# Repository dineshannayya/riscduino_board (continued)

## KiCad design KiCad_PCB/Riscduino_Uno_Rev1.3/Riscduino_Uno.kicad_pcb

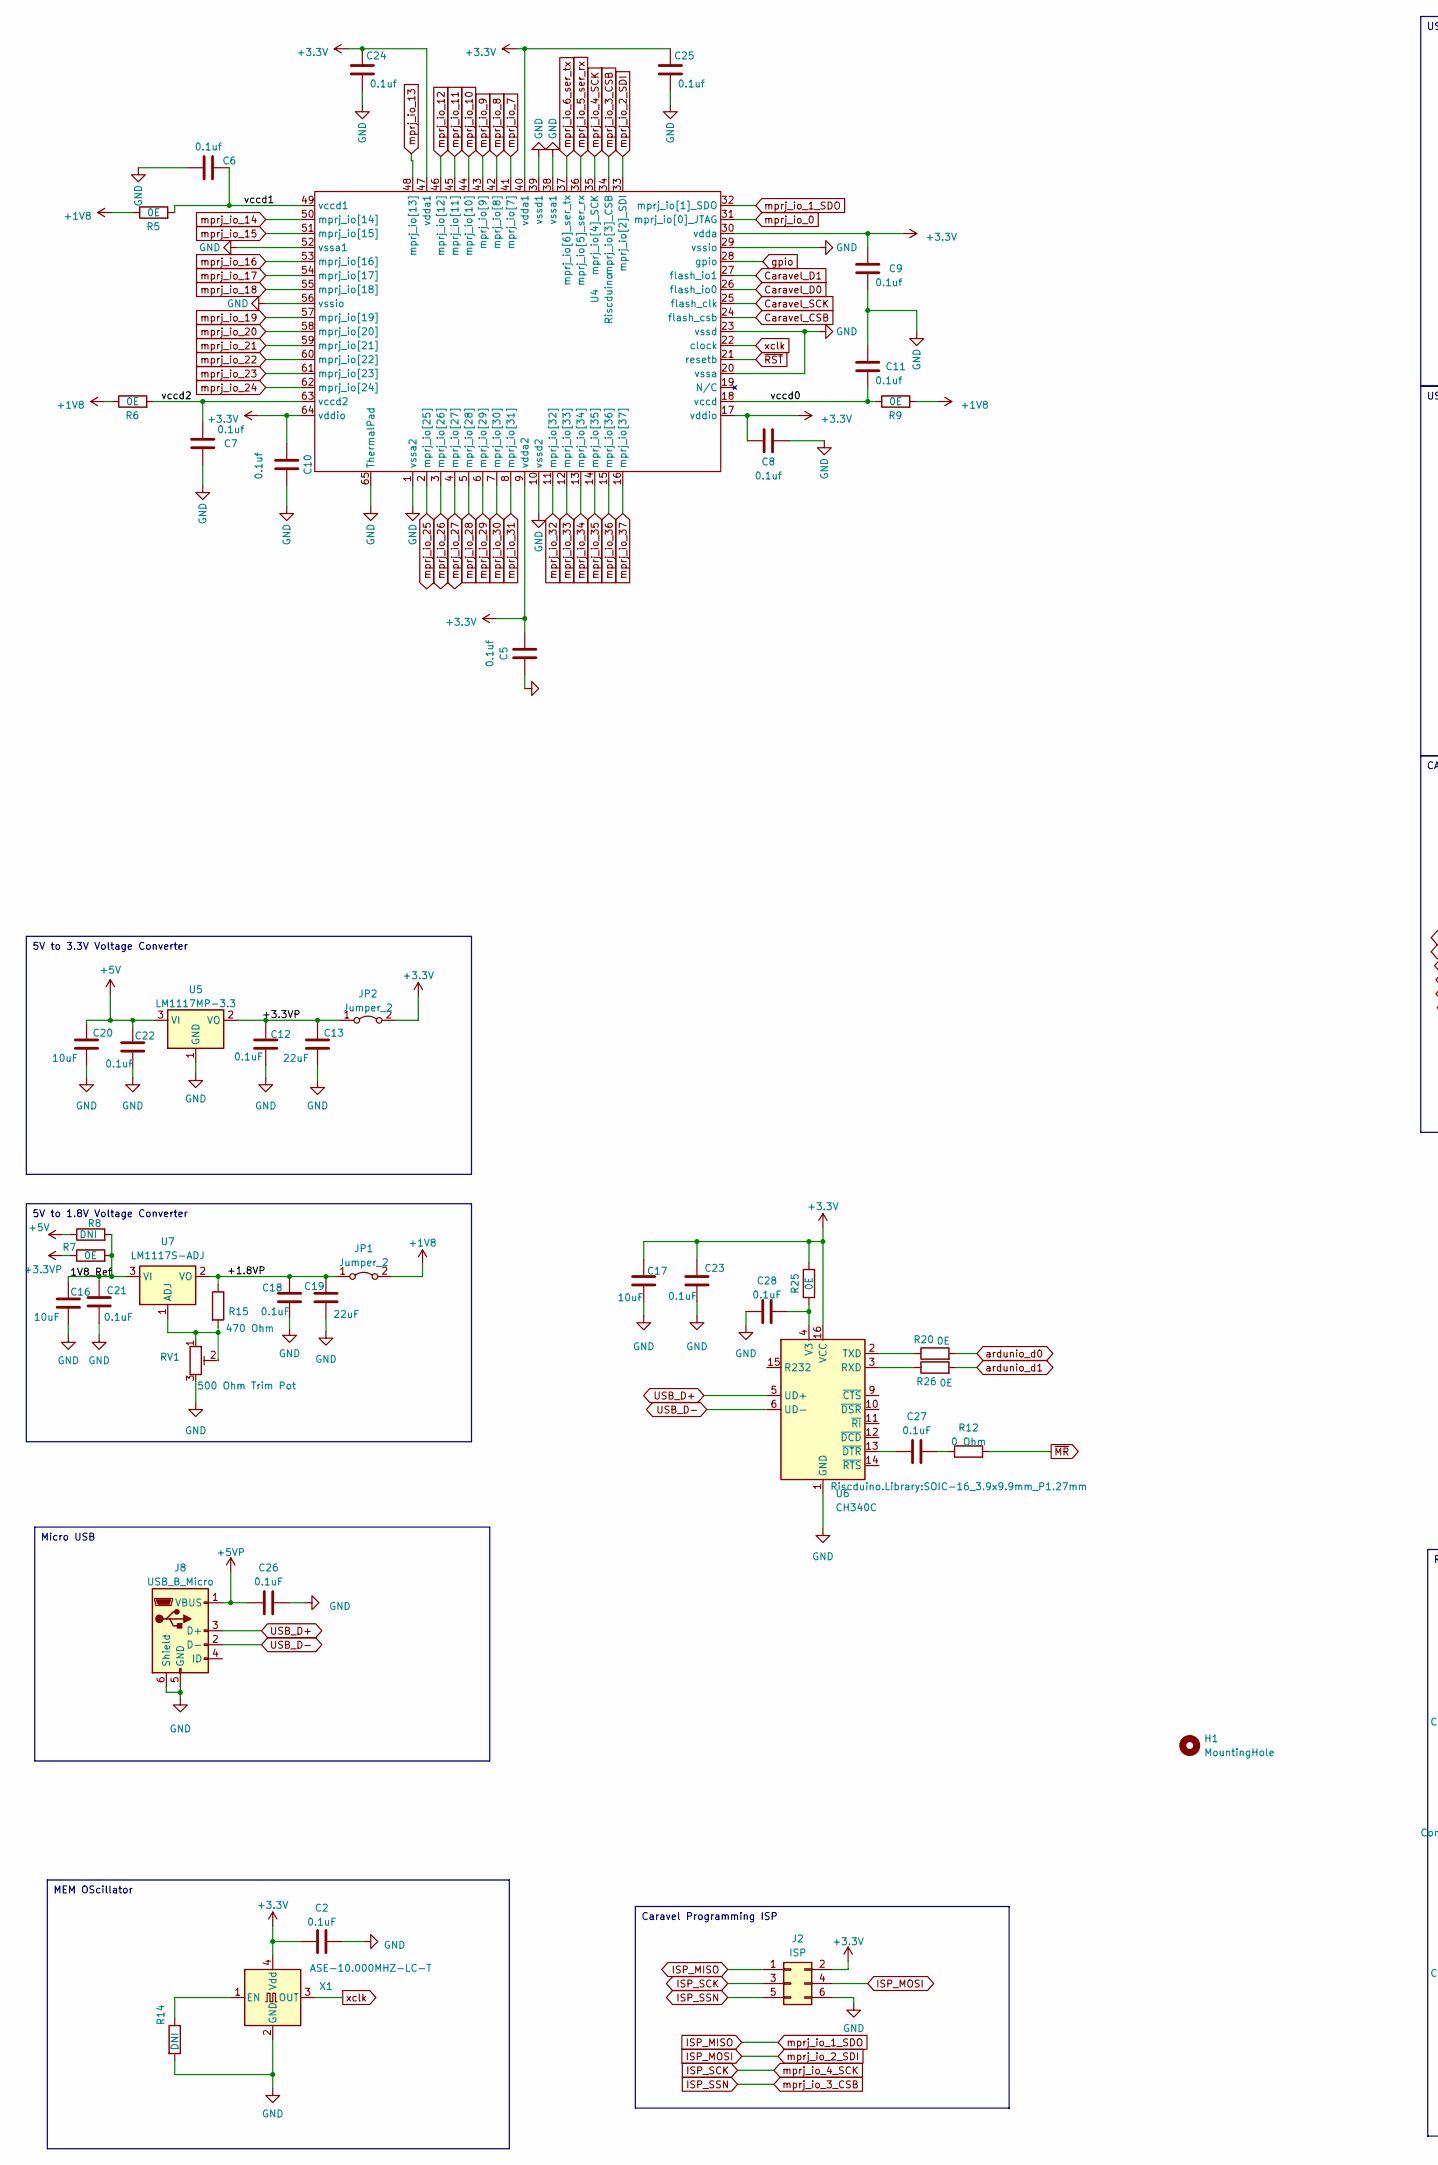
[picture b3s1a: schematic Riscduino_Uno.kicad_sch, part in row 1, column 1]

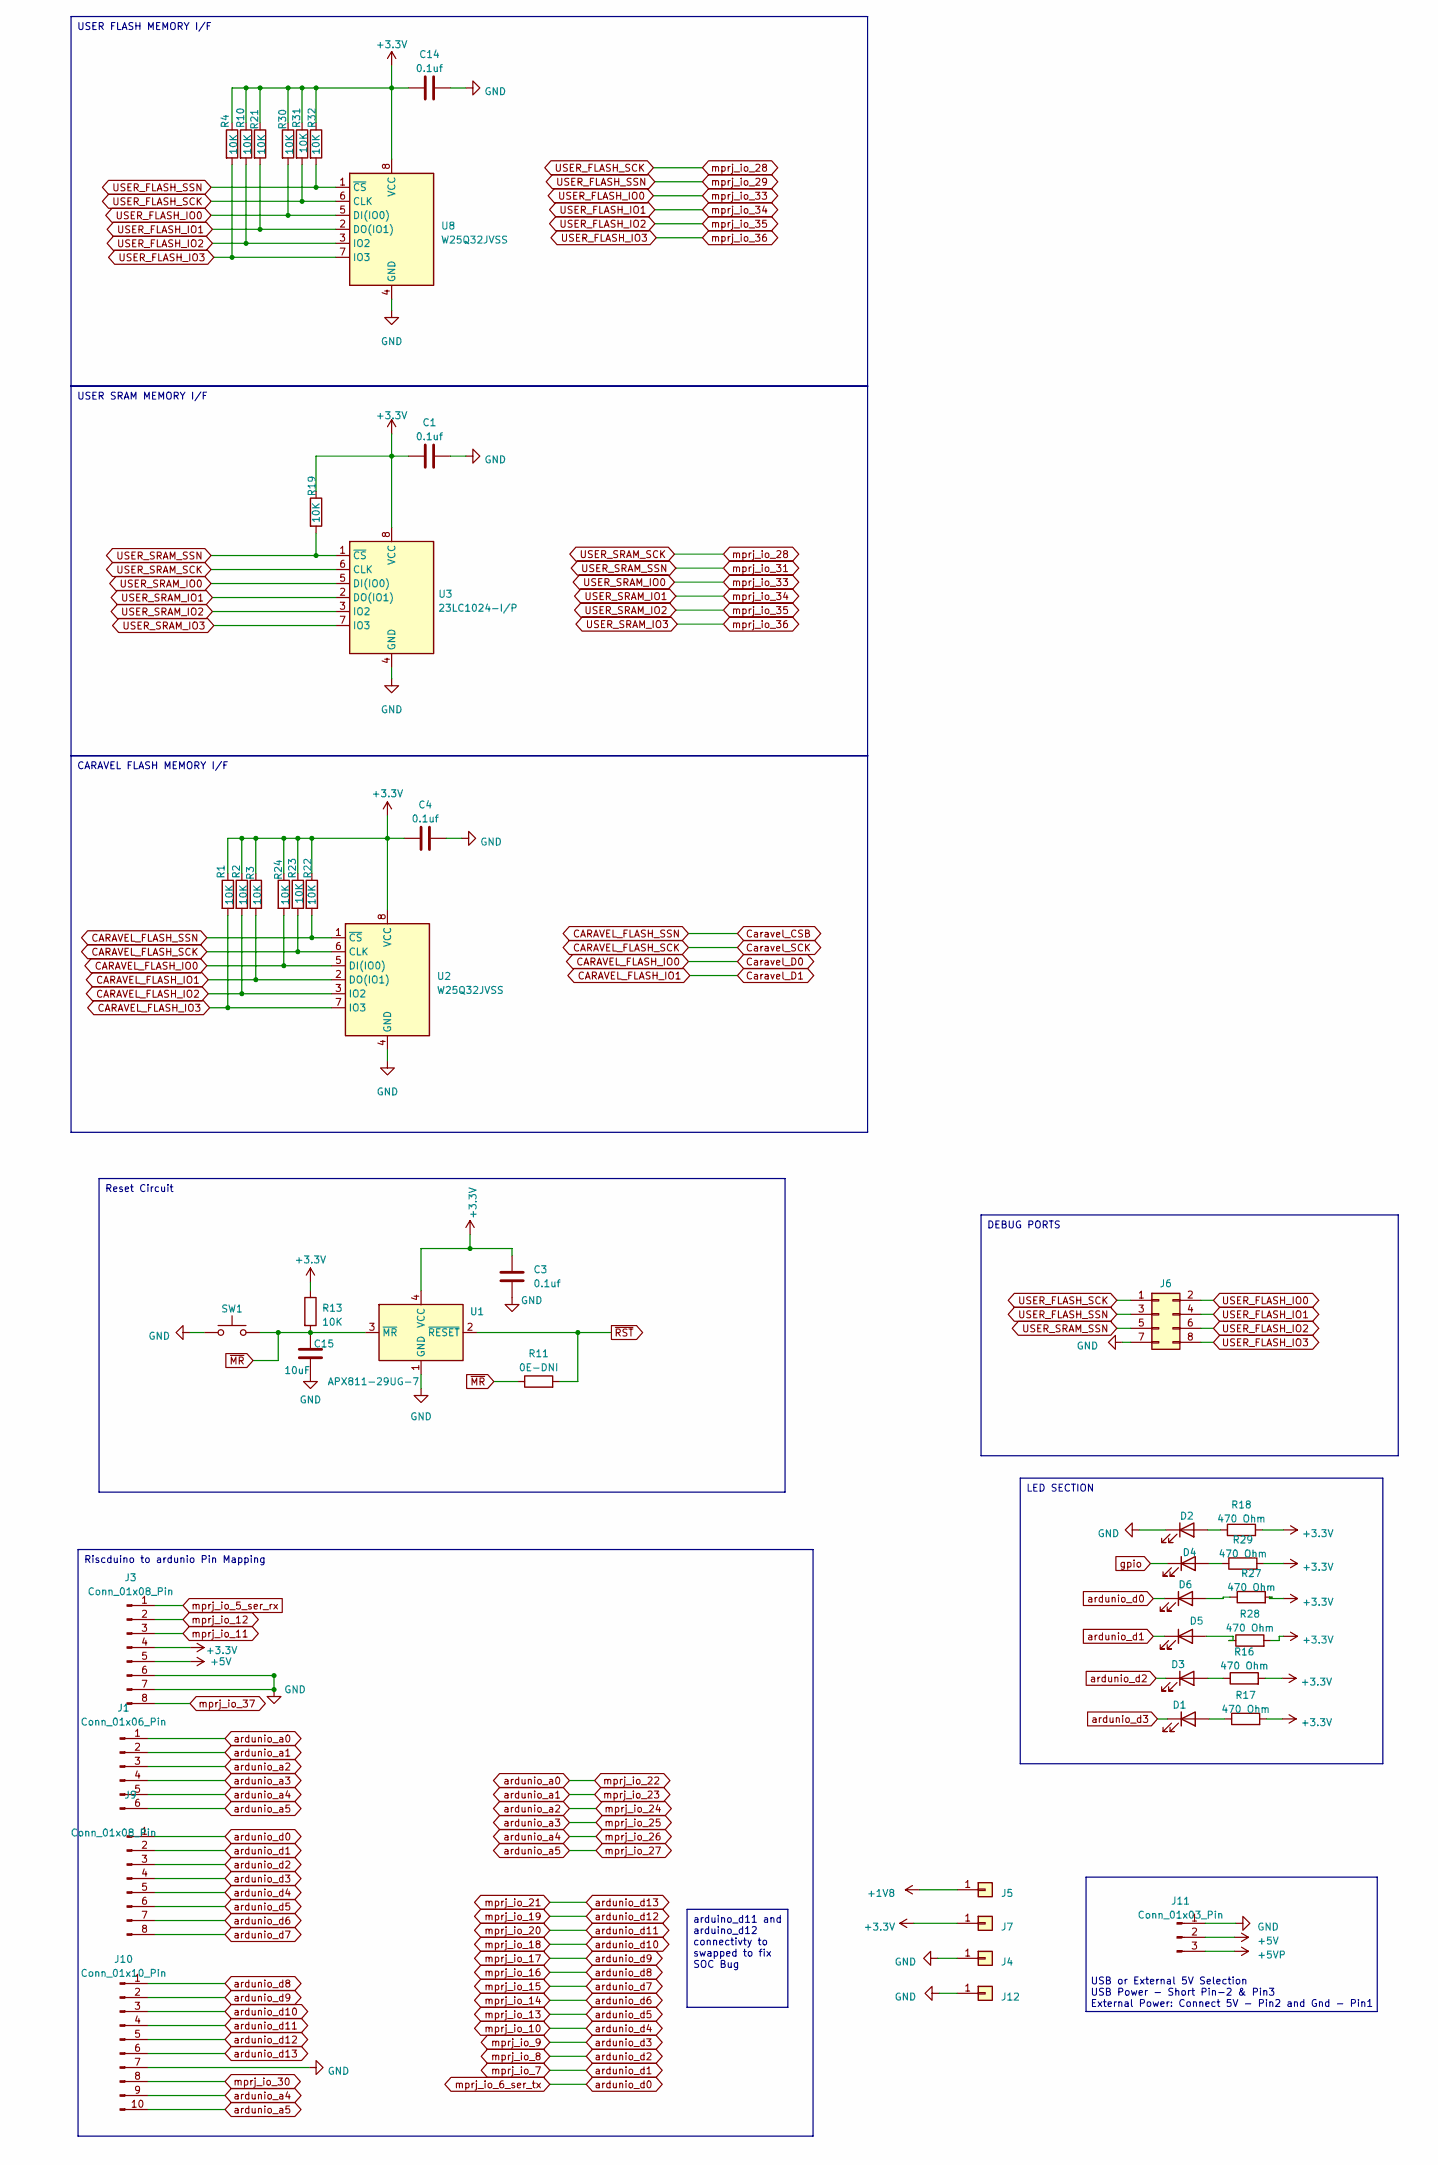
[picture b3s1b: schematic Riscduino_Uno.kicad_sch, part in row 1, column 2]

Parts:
C1, C3, C4, C5, C6, C7, C8, C9, C10, C11, C14, C24, C25: 0.1uf; C_0603_1608Metric_Pad1.08x0.95mm_HandSolder
C2, C12, C18, C21, C22, C23, C26, C27, C28: 0.1uF; C_0603_1608Metric_Pad1.08x0.95mm_HandSolder
C13, C19: 22uF; C_0805_2012Metric_Pad1.18x1.45mm_HandSolder
C15, C16, C17, C20: 10uF; C_0805_2012Metric_Pad1.18x1.45mm_HandSolder
D1, D2, D3, D4, D5: GREEN LED; LED_0805_2012Metric_Pad1.15x1.40mm_HandSolder
D6: BLUE LED; LED_0805_2012Metric_Pad1.15x1.40mm_HandSolder
H1: MountingHole; Arduino_UNO_R3_WithMountingHoles
J1: Conn_01x06_Pin; PinHeader_1x06_P2.54mm_Vertical
J2: ISP; PinHeader_2x03_P2.54mm_Vertical
J3, J9: Conn_01x08_Pin; PinHeader_1x08_P2.54mm_Vertical
J4, J5, J7, J12: Conn_01x01; PinHeader_1x01_P2.54mm_Vertical
J6: Conn_02x04_Odd_Even; PinHeader_2x04_P2.54mm_Vertical
J8: USB_B_Micro; USB_Micro-B_Molex-105017-0001
J10: Conn_01x10_Pin; PinHeader_1x10_P2.54mm_Vertical
J11: Conn_01x03_Pin; PinHeader_1x03_P2.54mm_Vertical
JP1, JP2: Jumper_2; PinHeader_1x02_P2.54mm_Vertical
R1, R2, R3, R4, R10, R13, R19, R21, R22, R23, R24, R30, R31, R32: 10K; R_0603_1608Metric_Pad0.98x0.95mm_HandSolder
R5, R6, R7, R9, R20, R25, R26: 0E; R_0603_1608Metric_Pad0.98x0.95mm_HandSolder
R8, R14: DNI; R_0603_1608Metric_Pad0.98x0.95mm_HandSolder
R11: 0E-DNI; C_0603_1608Metric_Pad1.08x0.95mm_HandSolder
R12: 0 Ohm; R_0603_1608Metric_Pad0.98x0.95mm_HandSolder
R15, R16, R17, R18, R27, R28, R29: 470 Ohm; R_0603_1608Metric_Pad0.98x0.95mm_HandSolder
RV1: 500 Ohm Trim Pot; Potentiometer_Bourns_3296W_Vertical
SW1: 4Pin Round Button SPST Straight Tactile Switch SM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; SW_SPST_EVPBF_TS4550TP
U1: APX811-29UG-7; SOT-143_Handsoldering
U2, U8: W25Q32JVSS; SOIC-8_5.23x5.23mm_P1.27mm
U3: 23LC1024-I/P; DIP-8_W7.62mm_LongPads
U4: Riscduino; RISCDUINO_QFN-64-1EP_9x9mm_P0.5mm_EP7.65x7.65mm_Ver1.1
U5: LM1117MP-3.3; SOT-223-3_TabPin2
U6: CH340C; SOIC-16_3.9x9.9mm_P1.27mm
U7: LM1117S-ADJ; SOT-223-3_TabPin2
X1: ASE-10.000MHZ-LC-T; Crystal_SMD_Abracon_ABM8G-4Pin_3.2x2.5mm

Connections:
+1V8: J5.1, JP1.2 (B), R5.1, R6.1, R9.2
+3.3V: C1.1, C2.1, C3.1, C4.1, C5.2, C8.2, C9.1, C10.2, C14.1, C17.1, C23.1, C24.1, C25.1, J2.2, J3.4, J7.1, JP2.2 (B), R1.1, R2.1, R3.1, R4.1, R10.1, R13.1, R16.2, R17.2, R18.2, R19.1, R21.1, R22.1, R23.1, R24.1, R25.2, R27.2, R28.2, R29.2, R30.1, R31.1, R32.1, U1.4 (VCC), U2.8 (VCC), U3.8 (VCC), U4.9 (vdda2), U4.17 (vddio), U4.30 (vdda), U4.40 (vdda1), U4.47 (vdda1), U4.64 (vddio), U6.16 (VCC), U8.8 (VCC), X1.4 (Vdd)
+3.3VP: C12.1, C13.1, JP2.1 (A), R7.1, U5.2 (VO)
+5V: C20.1, C22.1, J3.5, J11.2, R8.1, U5.3 (VI)
+5VP: C26.1, J8.1 (VBUS), J11.3
/+1.8VP: C18.1, C19.1, JP1.1 (A), R15.1, U7.2 (VO)
/vccd0: C11.2, R9.1, U4.18 (vccd)
/vccd1: C6.2, R5.2, U4.49 (vccd1)
/vccd2: C7.1, R6.2, U4.63 (vccd2)
CARAVEL_FLASH_IO0: R24.2, U2.5 (DI(IO0)), U4.26 (flash_io0)
CARAVEL_FLASH_IO1: R3.2, U2.2 (DO(IO1)), U4.27 (flash_io1)
CARAVEL_FLASH_IO2: R2.2, U2.3 (IO2)
CARAVEL_FLASH_IO3: R1.2, U2.7 (IO3)
CARAVEL_FLASH_SCK: R23.2, U2.6 (CLK), U4.25 (flash_clk)
CARAVEL_FLASH_SSN: R22.2, U2.1 (~CS), U4.24 (flash_csb)
GND: C1.2, C2.2, C3.2, C4.2, C5.1, C6.1, C7.2, C8.1, C9.2, C10.1, C11.1, C12.2, C13.2, C14.2, C15.2, C16.2, C17.2, C18.2, C19.2, C20.2, C21.2, C22.2, C23.2, C24.2, C25.2, C26.2, C28.1, D2.1 (K), J2.6, J3.6, J3.7, J4.1, J6.7, J8.5 (GND), J8.6 (Shield), J10.7, J11.1, J12.1, R14.2, RV1.3, SW1.1, U1.1 (GND), U2.4 (GND), U3.4 (GND), U4.1 (vssa2), U4.10 (vssd2), U4.20 (vssa), U4.23 (vssd), U4.29 (vssio), U4.38 (vssa1), U4.39 (vssd1), U4.52 (vssa1), U4.56 (vssio), U4.65 (ThermalPad), U5.1 (GND), U6.1 (GND), U8.4 (GND), X1.2 (GND)
ISP_MISO: J2.1, U4.32 (mprj_io[1]_SDO)
ISP_MOSI: J2.4, U4.33 (mprj_io[2]_SDI)
ISP_SCK: J2.3, U4.35 (mprj_io[4]_SCK)
ISP_SSN: J2.5, U4.34 (mprj_io[3]_CSB)
unnamed: C27.2, R12.1
unnamed 21: D1.2 (A), R17.1; also elsewhere on the board
unnamed: D2.2 (A), R18.1
unnamed: D3.2 (A), R16.1
unnamed: D4.2 (A), R29.1
unnamed: D5.2 (A), R28.1
unnamed: D6.2 (A), R27.1
unnamed: R26.1, U6.3 (RXD)
unnamed: R20.1, U6.2 (TXD)
unnamed: C28.2, R25.1, U6.4 (V3)
unnamed: C27.1, U6.13 (~DTR)
unnamed: R15.2, RV1.1, RV1.2, U7.1 (ADJ)
unnamed: C16.1, C21.1, R7.2, R8.2, U7.3 (VI)
unnamed: R14.1, X1.1 (EN)
USB_D+: J8.3 (D+), U6.5 (UD+)
USB_D-: J8.2 (D-), U6.6 (UD-)
USER_FLASH_IO0: J6.2, R30.2, U3.5 (DI(IO0)), U4.12 (mprj_io[33]), U8.5 (DI(IO0))
USER_FLASH_IO1: J6.4, R21.2, U3.2 (DO(IO1)), U4.13 (mprj_io[34]), U8.2 (DO(IO1))
USER_FLASH_IO2: J6.6, R10.2, U3.3 (IO2), U4.14 (mprj_io[35]), U8.3 (IO2)
USER_FLASH_IO3: J6.8, R4.2, U3.7 (IO3), U4.15 (mprj_io[36]), U8.7 (IO3)
USER_FLASH_SCK: J6.1, R31.2, U3.6 (CLK), U4.5 (mprj_io[28]), U8.6 (CLK)
USER_FLASH_SSN: J6.3, R32.2, U4.6 (mprj_io[29]), U8.1 (~CS)
USER_SRAM_SSN: J6.5, R19.2, U3.1 (~CS), U4.8 (mprj_io[31])
ardunio_a0: J1.1, U4.60 (mprj_io[22])
ardunio_a1: J1.2, U4.61 (mprj_io[23])
ardunio_a2: J1.3, U4.62 (mprj_io[24])
ardunio_a3: J1.4, U4.2 (mprj_io[25])
ardunio_a4: J1.5, J10.9, U4.3 (mprj_io[26])
ardunio_a5: J1.6, J10.10, U4.4 (mprj_io[27])
ardunio_d0: D6.1 (K), J9.1, R20.2, U4.37 (mprj_io[6]_ser_tx)
ardunio_d1: D5.1 (K), J9.2, R26.2, U4.41 (mprj_io[7])
ardunio_d2: D3.1 (K), J9.3, U4.42 (mprj_io[8])
ardunio_d3: D1.1 (K), J9.4, U4.43 (mprj_io[9]); also elsewhere on the board
ardunio_d4: J9.5, U4.44 (mprj_io[10])
ardunio_d5: J9.6, U4.48 (mprj_io[13])
ardunio_d6: J9.7, U4.50 (mprj_io[14])
ardunio_d7: J9.8, U4.51 (mprj_io[15])
ardunio_d8: J10.1, U4.53 (mprj_io[16])
ardunio_d9: J10.2, U4.54 (mprj_io[17])
ardunio_d10: J10.3, U4.55 (mprj_io[18])
ardunio_d11: J10.4, U4.58 (mprj_io[20])
ardunio_d12: J10.5, U4.57 (mprj_io[19])
ardunio_d13: J10.6, U4.59 (mprj_io[21])
gpio: D4.1 (K), U4.28 (gpio)
mprj_io_0: U4.31 (mprj_io[0]_JTAG)
mprj_io_5_ser_rx: J3.1, U4.36 (mprj_io[5]_ser_rx)
mprj_io_11: J3.3, U4.45 (mprj_io[11])
mprj_io_12: J3.2, U4.46 (mprj_io[12])
mprj_io_30: J10.8, U4.7 (mprj_io[30])
mprj_io_32: U4.11 (mprj_io[32])
mprj_io_37: J3.8, U4.16 (mprj_io[37])
xclk: U4.22 (clock), X1.3 (OUT)
~MR: C15.1, R11.1, R12.2, R13.2, SW1.2, U1.3 (~MR)
~RST: R11.2, U1.2 (~RESET), U4.21 (resetb)

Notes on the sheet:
MEM OScillator
5V to 3.3V Voltage Converter
LED SECTION
Riscduino to ardunio Pin Mapping
Micro USB
arduino_d11 and arduino_d12 connectivty to swapped to fix SOC Bug
USER SRAM MEMORY I/F
DEBUG PORTS
Caravel Programming ISP
USER FLASH MEMORY I/F
5V to 1.8V Voltage Converter
Reset Circuit
CARAVEL FLASH MEMORY I/F
USB or External 5V Selection USB Power - Short Pin-2 & Pin3 External Power: Connect 5V - Pin2 and Gnd - Pin1

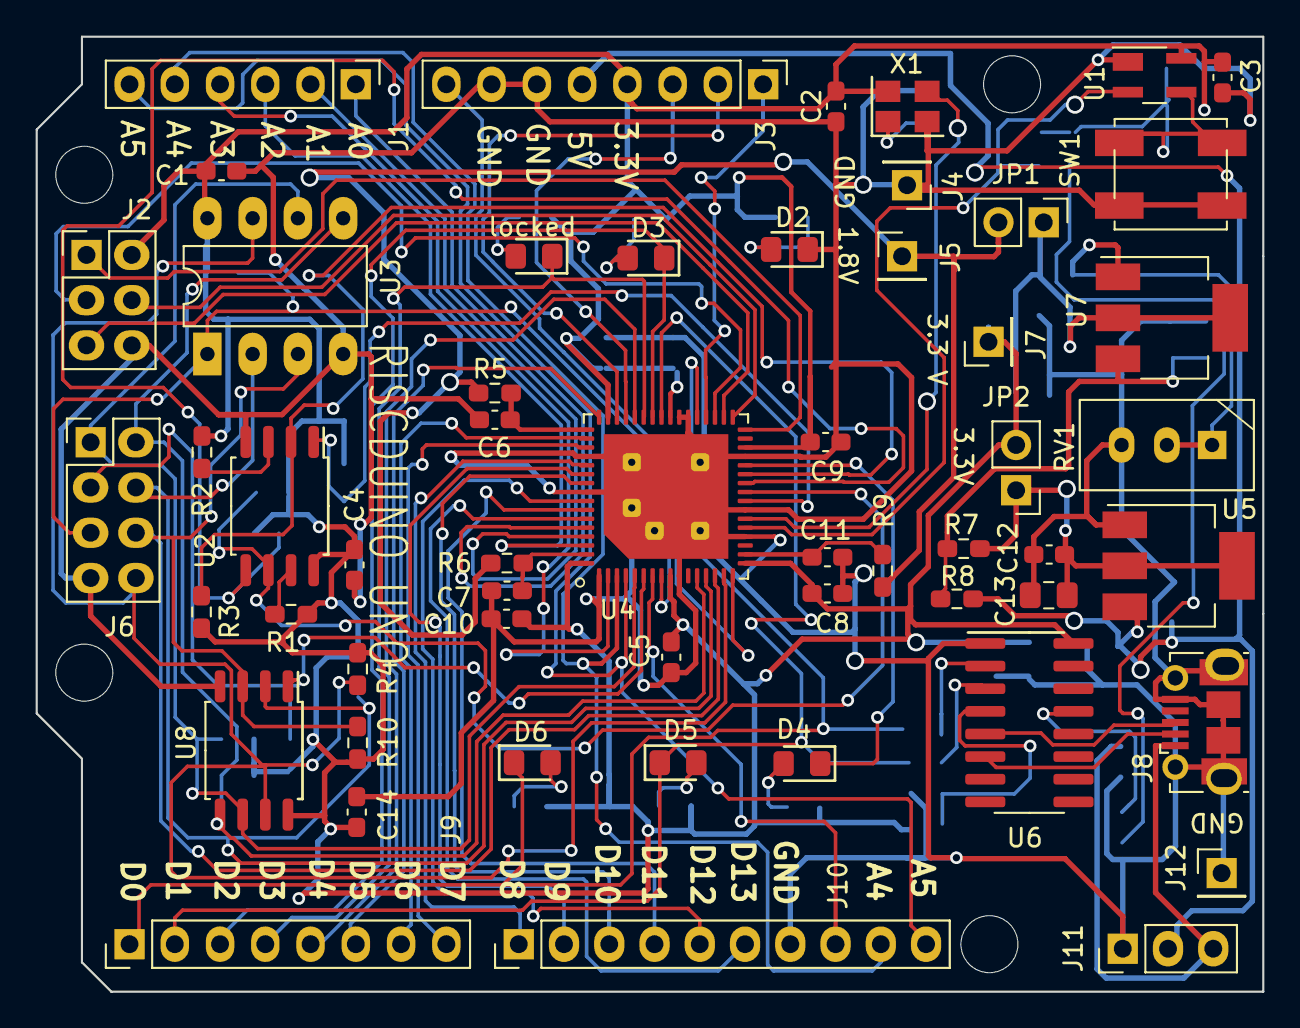
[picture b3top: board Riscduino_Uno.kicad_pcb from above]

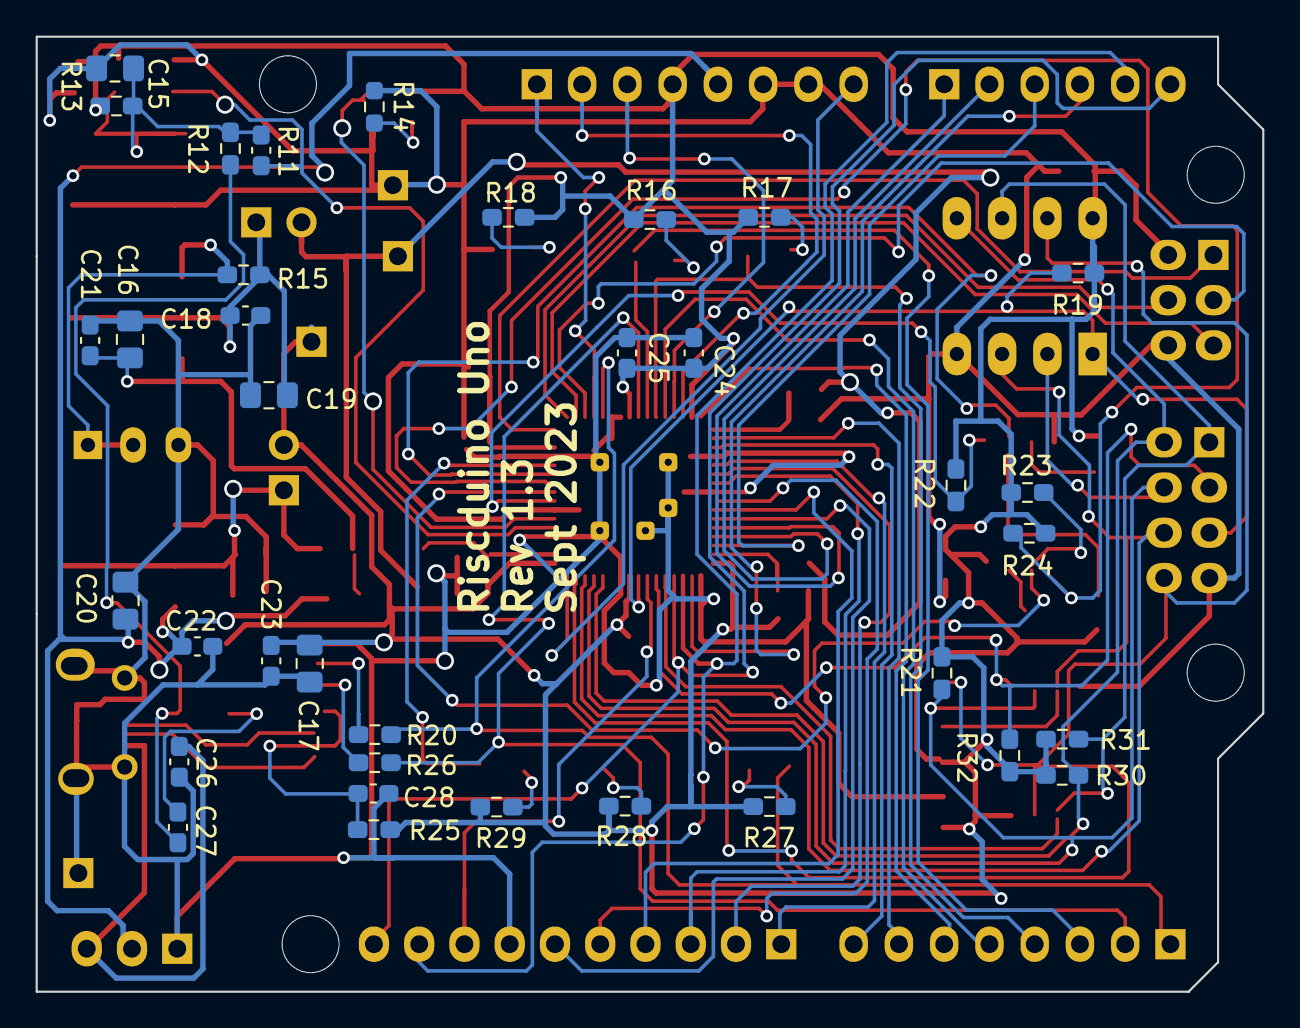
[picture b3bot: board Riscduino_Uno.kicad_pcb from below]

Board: 2 copper layers, 68.8 x 53.6 mm, 92 parts (36 on the bottom side), 72 nets.

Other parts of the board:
locked: GREEN LED; LED_0805_2012Metric_Pad1.15x1.40mm_HandSolder

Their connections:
unnamed 21: locked.2 (A); also elsewhere on the board
ardunio_d3: locked.1 (K); also elsewhere on the board

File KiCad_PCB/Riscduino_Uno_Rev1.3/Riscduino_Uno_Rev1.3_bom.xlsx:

Id | Designator | Footprint | Quantity | Designation | Supplier and ref | Column1 | _1
1 | J4,J12,J7,J5 | PinHeader_1x01_P2.54mm_Vertical (Male Berg Connector) | 4 | Conn_01x01
2 | JP2,JP1 | PinHeader_1x02_P2.54mm_Vertical (Male Berg Connector) | 2 | Jumper_2
3 | J11 | PinHeader_1x03_P2.54mm_Vertical (Male Berg Connector) | 1 | Conn_01x03_Pin
4 | J2 | PinHeader_2x03_P2.54mm_Vertical (Male Berg Connector) | 1 | ISP
5 | J6 | PinHeader_2x04_P2.54mm_Vertical(Male Berg Connector) | 1 | Conn_02x04_Odd_Even
6 | J10 | PinHeader_1x10_P2.54mm_Vertical(Female Berg Connector) | 1 | Conn_01x10_Pin
7 | J3,J9 | PinHeader_1x08_P2.54mm_Vertical(Female Berg Connector) | 2 | Conn_01x08_Pin
8 | J1 | PinHeader_1x06_P2.54mm_Vertical(Female Berg Connector) | 1 | Conn_01x06_Pin
9 | J8 | USB_Micro-B_Molex-105017-0001 | 1 | USB_B_Micro
10 | C2,C12,C27,C28,C18,C21,C22,C23,C26 | C_0603_1608Metric_Pad1.08x0.95mm_HandSolder | 9 | 0.1uF (100nf)
11 | C6,C14,C3,C7,C9,C10,C11,C5,C8,C4,C1,C24,C25 | C_0603_1608Metric_Pad1.08x0.95mm_HandSolder | 13 | 0.1uF (100nf)
12 | C13,C19 | C_0805_2012Metric_Pad1.18x1.45mm_HandSolder | 2 | 22uF
13 | C16,C17,C15,C20 | C_0805_2012Metric_Pad1.18x1.45mm_HandSolder | 4 | 10uF
14 | R9,R6,R7,R5,R12,R20,R25,R26 | R_0603_1608Metric_Pad0.98x0.95mm_HandSolder | 8 | 0E
15 | R18,R27,R28,R17,R16,R29,R15 | R_0603_1608Metric_Pad0.98x0.95mm_HandSolder | 7 | 470 Ohm
16 | R3,R2,R1,R4,R10,R13,R21,R32,R24,R22,R23,R30,R31,R19 | R_0603_1608Metric_Pad0.98x0.95mm_HandSolder | 14 | 10K
17 | D2,D3,D1,D4,D5 | LED_0805_2012Metric_Pad1.15x1.40mm_HandSolder | 5 | GREEN LED
18 | D6 | LED_0805_2012Metric_Pad1.15x1.40mm_HandSolder | 1 | BLUE LED
19 | U1 | SOT-143_Handsoldering | 1 | APX811-29UG-7
20 | U5 | SOT-223-3_TabPin2 | 1 | LM1117MP-3.3
21 | U8,U2 | SOIC-8_5.23x5.23mm_P1.27mm | 2 | W25Q32JVSS
22 | U7 | SOT-223-3_TabPin2 | 1 | LM1117S-ADJ
23 | U6 | SOIC-16_3.9x9.9mm_P1.27mm | 1 | CH340C
24 | U3 | DIP-8_W7.62mm_LongPads | 1 | 23LC1024-I/P
25 | U4 | RISCDUINO_QFN-64-1EP_9x9mm_P0.5mm_EP7.65x7.65mm_Ver1.1 | 1 | Riscduino
26 | SW1 | SW_SPST_EVPBF_TS4550TP | 1 | 4Pin Round Button SPST Straight Tactile Switch SMD - TS4550TP
27 | X1 | Crystal_SMD_Abracon_ABM8G-4Pin_3.2x2.5mm | 1 | ASE-10.000MHZ-LC-T
28 | RV1 | Potentiometer_Bourns_3296W_Vertical | 1 | 500 Ohm Trim Pot
Don't mount below componets
1 | H1 | Arduino_UNO_R3_WithMountingHoles | 1 | MountingHole
2 | R8 | R_0603_1608Metric_Pad0.98x0.95mm_HandSolder | 1 | DNI
3 | R11 | C_0603_1608Metric_Pad1.08x0.95mm_HandSolder | 1 | 0E-DNI
4 | R14 | R_0603_1608Metric_Pad0.98x0.95mm_HandSolder | 1 | DNI
